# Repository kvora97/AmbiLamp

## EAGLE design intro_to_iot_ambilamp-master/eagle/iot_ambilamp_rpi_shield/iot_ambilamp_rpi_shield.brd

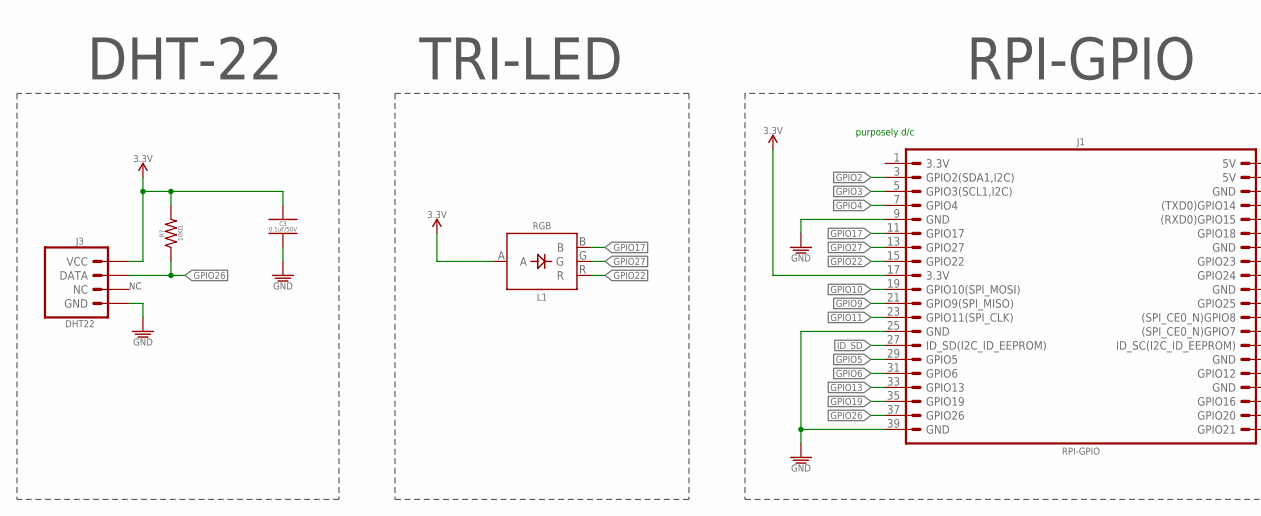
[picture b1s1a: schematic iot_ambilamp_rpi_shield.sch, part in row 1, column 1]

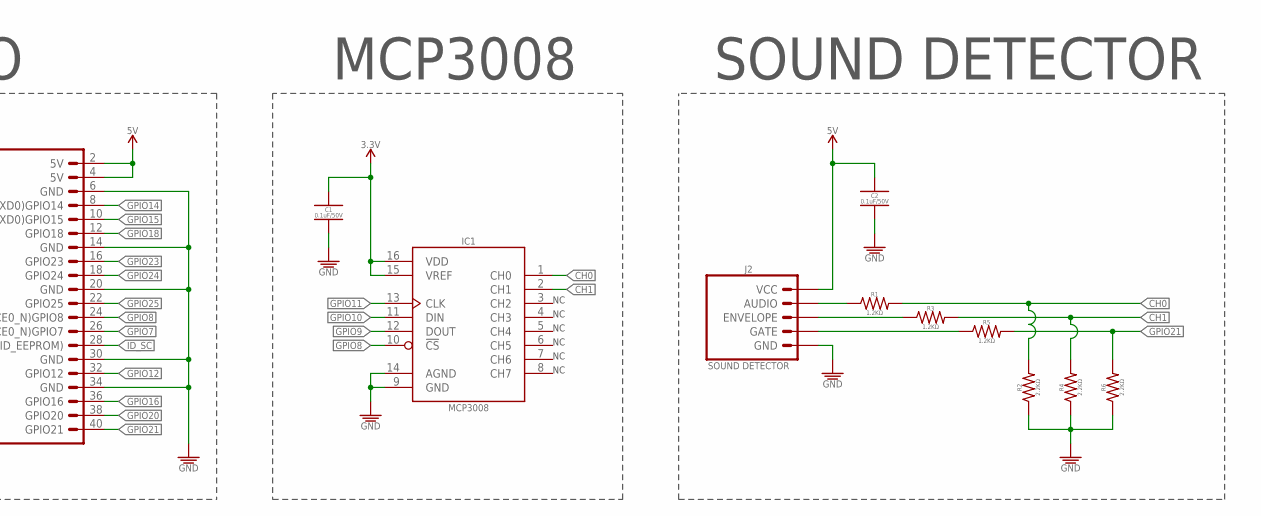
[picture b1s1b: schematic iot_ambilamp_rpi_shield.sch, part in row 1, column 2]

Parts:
C1, C2, C3: 0.1uF/50V; CAP_CER_SMD-805
IC1: MCP3008; SO-16
J1: RPI-GPIO; CONNECTOR_RPI-GPIO
J2: SOUND DETECTOR; CONNECTOR-RA_SOUND-DETECTOR_SPARKFUN
J3: DHT22; CONNECTOR_TEMPERATURE-SENSOR_DHT22
L1: RGB; LED-5MM-PTH_RGB-CA
R1, R3, R5: 1.2KΩ; RESC2012X60_HS
R2, R4, R6: 2.2KΩ; RESC2012X60_HS
R7: 10KΩ; RESC2012X60_HS

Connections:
3.3V: C1.1, C3.1, IC1.15 (VREF), IC1.16 (VDD), J1.17 (3.3V), J3.VCC, L1.A, R7.2
5V: C2.1, J1.2 (5V), J1.4 (5V), J2.VCC
CH0: IC1.1 (CH0), R1.2, R2.2
CH1: IC1.2 (CH1), R3.2, R4.2
GND: C1.2, C2.2, C3.2, IC1.9 (GND), IC1.14 (AGND), J1.6 (GND), J1.9 (GND), J1.14 (GND), J1.20 (GND), J1.25 (GND), J1.30 (GND), J1.34 (GND), J1.39 (GND), J2.GND, J3.GND, R2.1, R4.1, R6.1
GPIO2: J1.3 (GPIO2(SDA1,I2C))
GPIO3: J1.5 (GPIO3(SCL1,I2C))
GPIO4: J1.7 (GPIO4)
GPIO5: J1.29 (GPIO5)
GPIO6: J1.31 (GPIO6)
GPIO7: J1.26 ((SPI_CE0_N)GPIO7)
GPIO8: IC1.10 (!CS), J1.24 ((SPI_CE0_N)GPIO8)
GPIO9: IC1.12 (DOUT), J1.21 (GPIO9(SPI_MISO))
GPIO10: IC1.11 (DIN), J1.19 (GPIO10(SPI_MOSI))
GPIO11: IC1.13 (CLK), J1.23 (GPIO11(SPI_CLK))
GPIO12: J1.32 (GPIO12)
GPIO13: J1.33 (GPIO13)
GPIO14: J1.8 ((TXD0)GPIO14)
GPIO15: J1.10 ((RXD0)GPIO15)
GPIO16: J1.36 (GPIO16)
GPIO17: J1.11 (GPIO17), L1.B
GPIO18: J1.12 (GPIO18)
GPIO19: J1.35 (GPIO19)
GPIO20: J1.38 (GPIO20)
GPIO21: J1.40 (GPIO21), R5.2, R6.2
GPIO22: J1.15 (GPIO22), L1.R
GPIO23: J1.16 (GPIO23)
GPIO24: J1.18 (GPIO24)
GPIO25: J1.22 (GPIO25)
GPIO26: J1.37 (GPIO26), J3.DATA, R7.1
GPIO27: J1.13 (GPIO27), L1.G
ID_SC: J1.28 (ID_SC(I2C_ID_EEPROM))
ID_SD: J1.27 (ID_SD(I2C_ID_EEPROM))
unnamed: J2.GATE, R5.1
unnamed: J2.ENVELOPE, R3.1
unnamed: J2.AUDIO, R1.1

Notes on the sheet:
MCP3008
RPI-GPIO
TRI-LED
SOUND DETECTOR
DHT-22
purposely d/c

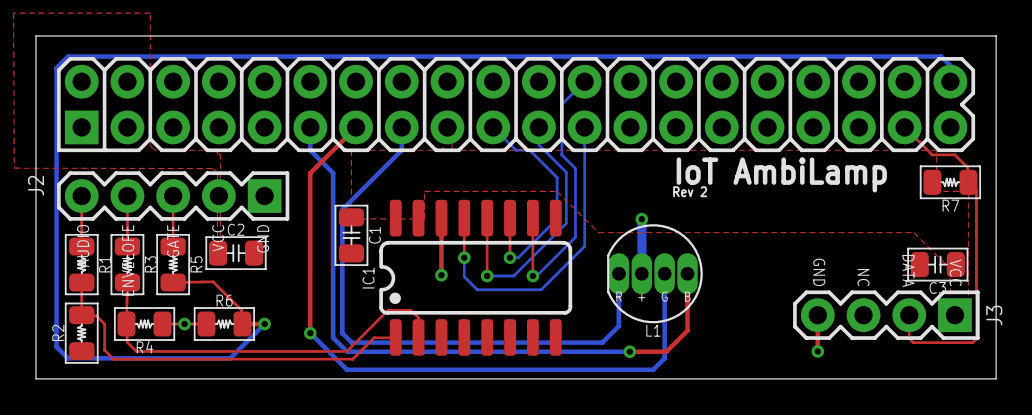
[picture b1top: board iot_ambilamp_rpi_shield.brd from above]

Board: 2 copper layers, 53.3 x 19.0 mm, 15 parts (0 on the bottom side), 17 nets.

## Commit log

2017-10-16 init with boilerplate html
2017-10-23 Finished P1
2017-10-24 Finished P1 with required updates
2017-10-24 Last Commit Tuesday Morning
2017-10-25 Added image files
2017-10-25 declone
2017-10-25 Added PHP Files
2017-10-25 Added more PHP functionality
2017-10-30 Finished Challenge 3
2017-10-30 Added php file for database interaction
2017-10-31 Sensors reading and printing values
2017-11-01 Temperature and Humidity collections readings are fine
2017-11-02 P2 Finished
2017-11-02 Started P3
2017-11-09 Working on Challenge 2
2017-11-13 Finished P3 Challenge 1
2017-11-14 Finished P3 Challenge 2
2017-11-15 Finished P3 Challenge 3
2017-11-15 Started P3 Challenge 4
2017-11-15 Almost Finished P3 Challenge 4
2017-11-15 Finished P3
2017-11-18 Added box pdf file
2017-11-18 Added svg file 3-D printing box container
